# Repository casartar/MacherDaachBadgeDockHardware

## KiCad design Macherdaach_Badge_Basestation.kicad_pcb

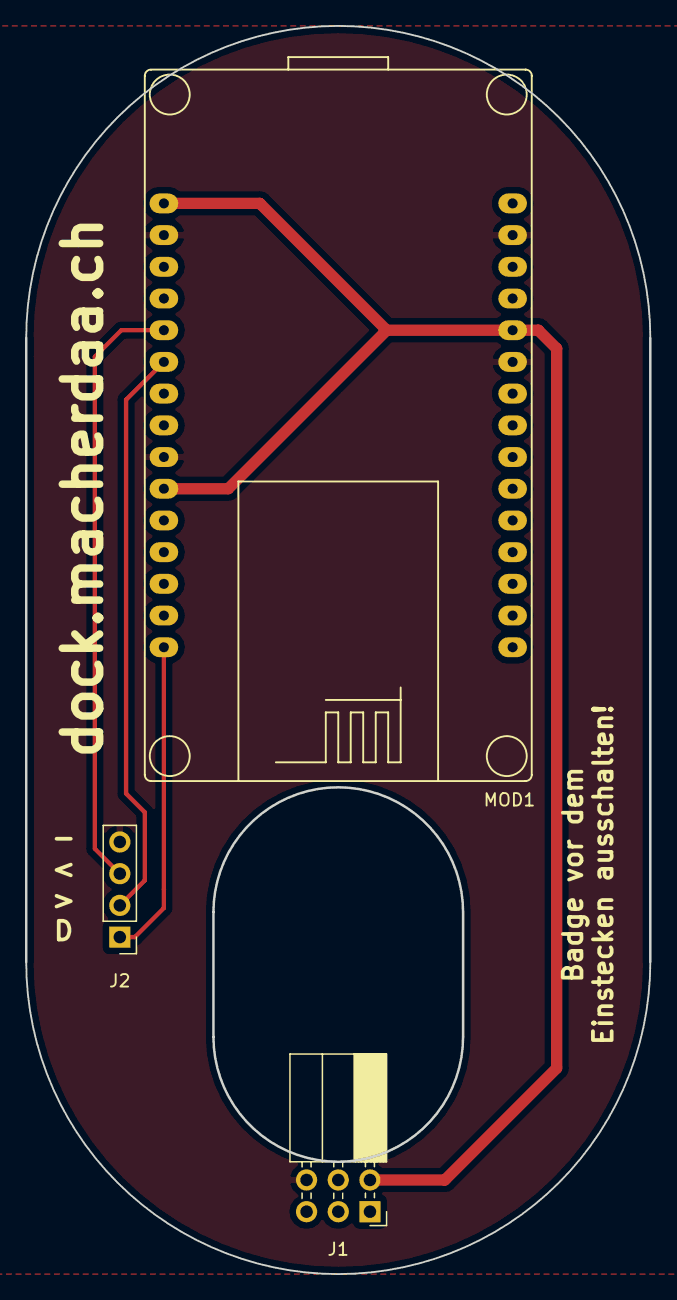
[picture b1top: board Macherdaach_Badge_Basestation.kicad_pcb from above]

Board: 2 copper layers, 50.0 x 100.0 mm, 3 parts (0 on the bottom side), 5 nets.

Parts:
J1: AVR-ISP-HEADER; PinSocket_2x03_P2.54mm_Horizontal
J2: Conn_01x04_Male; PinHeader_1x04_P2.54mm_Vertical
MOD1: NodeMCU; NodeMCU_v0.1

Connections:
+3V3: J1.2, MOD1.11, MOD1.16, MOD1.25
/D0: J2.1, MOD1.30
/D7: J2.2, MOD1.21
/D8: J2.3, MOD1.20
GND: J1.6, J2.4, MOD1.10, MOD1.14, MOD1.17, MOD1.24

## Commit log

2019-07-09 no idea what i did there
2019-07-14 changed NodeMCU board v1.0 to v0.1 which is bigger
2019-07-16 Adjustet some componenets and reanotation
